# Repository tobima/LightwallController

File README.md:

LightwallController
===================

System
------

Based on the following hardware:
- ARM-Cortex-M4 STM32F407
- STM32F4DIS-BB (Base Board with Ethernet, RS232, MicroSD card slot)

Adaption to the Hardware could be found in the `Hardware folder` ;-)

Software
--------

The manual to setup the development environment can be found at:
http://www.ccc-mannheim.de/wiki/Chibios

After the first download the following script must be executed:
```
InitSubModules.sh
```
Building and flashing:
```
cd Firmware
make
make flash (USB must be reconnected, if flashing failed)
```

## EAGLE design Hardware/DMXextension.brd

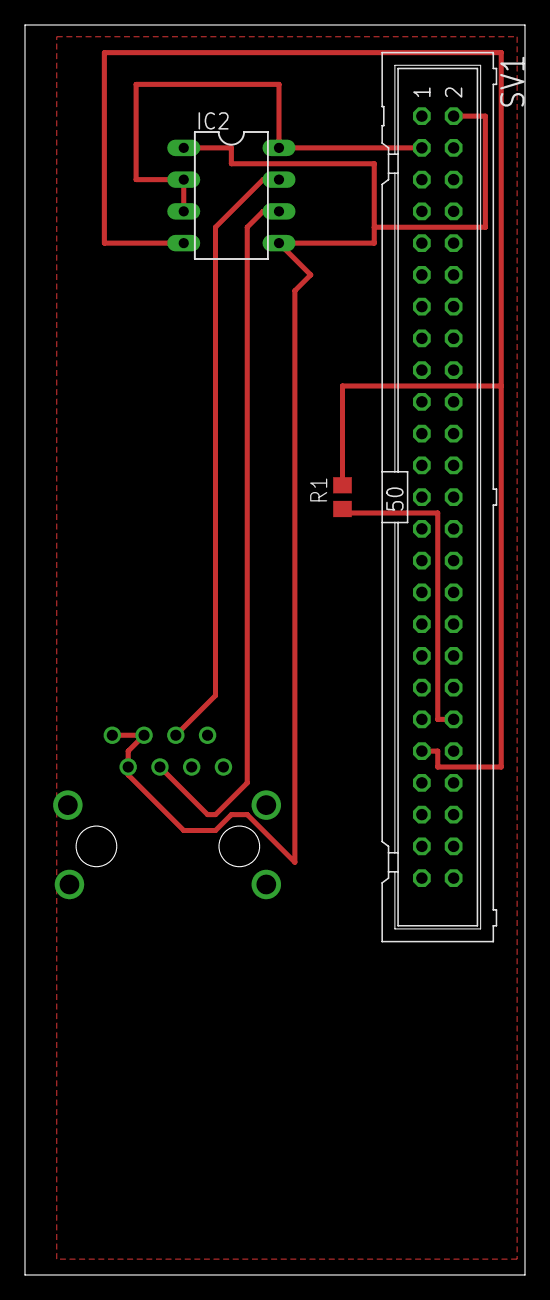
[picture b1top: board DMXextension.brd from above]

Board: 2 copper layers, 40.0 x 100.0 mm, 4 parts (1 on the bottom side), 6 nets.

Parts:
IC2: 75176AP; DIL08
R1: 100; R0805
SV1: ML50
X1: RJ45

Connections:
+5V: IC2.2, IC2.3, IC2.8, SV1.3
GND: IC2.1, IC2.5, SV1.2, X1.6, X1.7, X1.8
GPIOD8: R1.1, SV1.40
GPIOD9: IC2.4, R1.2, SV1.41
unnamed: IC2.7, X1.4
unnamed: IC2.6, X1.5

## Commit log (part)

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2013-05-19 Get USART 6 to work on STMF32DIS-BB evalboard
2013-05-19 add .gitignore
2013-05-26 ethernet stack is working
2013-06-12 Working test system: dmx, sdcard, web server ..
2013-08-24 moved board configuration to own repository
2013-08-24 Updating submodule 'board'
2013-08-28 Update patch for infint loop on mac start
2013-08-28 moved Chibios to lib folder and build folder and Makefile one folder up.
2013-08-28 update board repo
2013-08-28 remove patch. Set ETH1 PHY Power state change to fakse instead.
2013-08-30 Environment cleaning
2013-08-30 Use the Chibios branch of fc_c
2013-08-30 First version of makefile extension in fc_c
2013-08-30 The Makefile uses the fc_c repository
2013-08-30 First try to use fc code in the new environment
2013-09-01 Included the new functionality of fc_c into the project
2013-09-06 Correct aligning for the Microcontroller
2013-09-06 Code for displaying a frame
2013-09-06 Updated fullcircle library
2013-09-22 Upper case and lower case fullcircle files are recogniced
2013-09-27 Some more comments
2013-09-27 Updated Chibios Project
2013-09-27 Small test programm to modify the DMX
2013-09-27 Added some description for the Hardware to build
2013-10-03 Debug interface to display actual DMX buffer
2013-10-03 Restarted DMX project using a random PIN
2013-10-03 More tests with r0ket portation
2013-10-03 Some more comments in DMX
2013-10-03 DMX commandline tool can also decrease the size of the transmitted universe
2013-10-03 Updated the Layout of the DMX extension
2013-10-04 Included some lost changes
2013-10-05 Some measured timings from the Oszi
2013-10-06 Removed unknown code
2013-10-12 Increased the downpull to indicate the start
2013-10-12 Included the routed extension shield
2013-10-18 Added another parameter, to specify the sleeptime between two frames
2013-10-26 Add net shell
2013-10-28 Prepared thread for the dynamic fullcircle protocol
2013-10-28 Endless thread is running until infinity and beyond
2013-10-29 Updated IP address
2013-10-29 Some first steps to use the mailbox
2013-10-29 Also added initialization
2013-10-30 New Fcserver implementation with another callback
2013-11-01 Some tests with the mailbox
2013-11-01 Some more tests
2013-11-01 Reset dmx break time to 125µs
2013-11-01 FC updated
2013-11-01 Mailbox works (again)
2013-11-01 Give the server an pointer to a shell, and he will write on it
2013-11-01 Debugging interface can be activated via commandline + Makefile has necessary define
2013-11-01 add ini parser from https://code.google.com/p/inih/
2013-11-01 Chibios network code
2013-11-01 Only check the mailbox, if there is something inside
2013-11-01 Use new dependency in fc_c
2013-11-01 Better debugging messages
2013-11-01 Deactivated debugging in fc_c library
2013-11-01 wrapped logging for the dynamic fc thread
2013-11-01 Beta Implementation of the server
2013-11-01 Network config could be read from sdcard
2013-11-02 Wrapped comments
2013-11-02 update make rules
2013-11-02 Renamed to other file format
2013-11-02 Moved defines also into the seperate main file
2013-11-05 New library version of fc_c
2013-11-07 Network configuration
2013-11-07 The resolution can be extracted
2013-11-07 Debug output for the mapping logic
2013-11-07 Removed debugging
2013-11-07 Rebuild old code, to give always a new file to the user
2013-11-07 Searching in the root folder of the SDcard is working
2013-11-07 tree command can use a root folder to search in
2013-11-07 The first file is sent back to the user
2013-11-08 Moved sequence file - playing logic into a seperate module
2013-11-08 The files are listed one after the other
2013-11-08 Display only valid paths
2013-11-08 With enough memory sequences can be played automatically
2013-11-08 Initialize the SDcard at the beginning
2013-11-08 Returnvalue for fcstatic_playfile and removed debug comment
2013-11-08 fc_c updated
2013-11-08 Dimming is working
2013-11-08 Removed debug code
2013-11-09 ifconfig has more detailed output; interface can be modified manually
2013-11-09 ifconfig commandline improved
2013-11-09 Refactoring started
2013-11-09 Moved file sending functionality directly into the scheduler
2013-11-09 Blue LED indicating DMX output
2013-11-09 Do not start the fullcircle server thread
2013-11-09 Dynamic server integrated into the Scheduler
2013-11-10 Debuggin in Scheduler decreased
2013-11-11 Fixed status LED
2013-11-12 Button presses are only detected once
2013-11-12 Switch back to final Scheduler logic
2013-11-12 Debug the dynamic protocol again -> Debugging has been activated
2013-11-12 webserver läuftgit add src/web/io.c
2013-11-15 New library
2013-11-15 Removed debug argument
2013-11-15 New configuration reading abstraction
2013-11-15 Cleaned more code from the server logic
2013-11-15 call the mapping functionality from the server functionality
2013-11-16 Finialized interface between fcserver and scheduler
2013-11-26 Comments adapted
2013-11-26 spelling found
2013-11-28 Removed detailed debugging from the configuration
2013-11-29 Beta version of statemachine
2013-11-30 Updated the state diagram
2013-12-06 Interface has its necessary logic
2013-12-06 Blubb
2013-12-06 set the status corretly
2013-12-06 Refactored Mailbox for dynamic server
2013-12-06 New command to disconnect all clients prepared
2013-12-07 New server API is also used correctly on the uC
2013-12-07 Initialize also the return value
2013-12-07 Supervision of the dynamic network code
2013-12-07 Also use milliseconds for the scheduling monitoring
2013-12-07 Only change if we are not deactivated
2013-12-07 Display timeout for incoming frames of the network
2013-12-07 Read configuration
2013-12-07 Corrected configuration parsing (with debugging activated)
2013-12-07 Read the configuration from the SDcard and deactivate the scheduler if necessary
2013-12-12 Gitsubmodule changes
2013-12-27 More debug code
2013-12-27 Started to implement start mechanism for scheduler
2013-12-27 Improved configuration file parsing
2013-12-27 fc library changes
2013-12-28 Changes in the fc library
2013-12-30 Prepared GFX
2013-12-30 Moved copied code from Kaeptn into a new c module
2013-12-30 LEDs neu geordnet
2013-12-30 vprintf into an text buffer (compiling, but more)
2013-12-30 Fixed the orientation of the virtual wall on the LCD Added text output on the screen.
2013-12-30 The client status is visualized on the LCD
2013-12-30 IP address of connecting client is displayed
2013-12-30 Network status codes are displayed in Lightgrey
2013-12-30 Began with timeout visualisazion
2013-12-31 Use another timer for DMX
2014-01-03 Changes the Timer of DMX to another timer
2014-01-03 Moved initialization up into the beginning
2014-01-10 DMX and LCD paralell usage prepared
2014-01-10 Some blank lines moved around
2014-01-12 So nobody must do higher math in his brain
2014-01-12 Reduce compiler warnings
2014-01-13 Shell available via USB
2014-01-13 Found a diff, that was forgotten
2014-02-21 Minimal version generated, where no SDCard or ethernet is supported
2014-03-08 Better Makefile-flag name
2014-03-08 Moved board configuration to a place, where it can be changed (necessary for LCD usage)
2014-03-29 Starting input stuff
2014-04-14 Use a temporary buffer, and only update DMX buffer on valid values
2014-04-14 Added rgb command (all fullcircle lamps)
2014-04-18 Prepared fading with rainbow color algorithm
2014-04-18 Inserted fading algorithm with debug code
2014-04-19 Refactored color fading algorithm, now more portable by using callback function
2014-04-21 fixed makefile, added duration parameter one level deeper
2014-04-21 Added I2C, necessary for touchscreen
2014-04-21 Activate USB Serial interface
2014-04-21 Debug output, when a button was pressed added
2014-04-22 Moved local function to its correct place
2014-04-22 Rebuild visualization with windows
2014-04-22 Second window can be displayed, but is in background :-/
2014-04-22 Overlayed window can coexist
2014-04-22 New module responsible with the logic for the buttons
2014-04-22 Made callbacks for touchscreen accessable for other modules
2014-04-22 Moved calibration it the target
2014-04-22 Storing configuration on FAT (sdcard) in a seperate thread
2014-04-22 activated reading of the configuration
2014-04-22 Added second button, for manual testing logic
2014-04-23 Cleaned up code
2014-04-23 Rearranged SD card initialization
2014-04-23 Comments
2014-04-25 Toggeling manual testing prepared
2014-04-25 Inserted macros for debug output
2014-04-25 Added logic to the manual button (starting the server again is not running)
2014-04-25 First example for accessing the flash added
2014-04-25 Added command into the main function
2014-04-25 Fixed newline
2014-04-25 Still changing
2014-04-25 Starting flashing
2014-04-25 Removed unused files
2014-05-29 Merging complete
2014-05-29 Cleared warning with cast
2014-05-29 Minifixing
2014-05-29 added missing C-sources
2014-05-29 removed redundant code
2014-06-01 Flash test util improved
2014-06-01 removed unused definitions
2014-06-01 better output of the flash test util
2014-06-01 Flash test util can use specific memory blocj
2014-06-01 writing the flash is working
2014-06-01 Touch screen calibration data is stored in the FLASH
2014-06-02 commandline interface for UI added
2014-06-02 debug output when writing into the flash
2014-06-02 insert erasing into access logic to the flash (only used once... timing problem) Also the flash is accessed as one big memory area (no longer block wise)
2014-06-08 Erase flash before storing there a new configuration
2014-06-09 Spelling fixed
2014-06-10 Updated flashing command in the Makefile
2014-06-10 Wait for the fcscheduler to stop
2014-06-11 Project uses FatFswrapping logic
2014-06-11 wrapper successful integrated
2014-06-11 further tweaks in the commandline ugfx util
2014-06-11 Moved the GUI update into the main-loop
2014-06-13 Began with new module for an independet dmx buffer visualization
2014-06-13 more logic inserted in the module to display the DMX on the LCD
2014-06-13 comment
2014-06-13 dummy thread for ugfx tested successfully
2014-06-13 DMX buffer is visualized
2014-06-14 Cleanup of the cleanup
2014-06-18 Added mouse events in order to select a box
2014-06-18 Box can be selected
2014-06-18 Print the coordinate from the select box
2014-06-26 Comments and fixed includes
2014-06-29 First idea of the new interface
2014-06-29 Code is compiling again after the refactoring
2014-06-29 Removed a warning :-)
2014-06-29 fc_c updates
2014-06-30 updated macro disabeling
2014-06-30 display correct framebuffer in debug output
2014-06-30 New GDB configuration integrated
2014-06-30 More checks for the visualization thread
2014-07-05 included new thread to superivise the button
2014-07-05 with more memory, the GUI is displayed
2014-07-05 seperate command added to stop the visualization thread
2014-07-05 Box selection works a little bit better
2014-07-05 Added function to detect boxes hidded by the menu
2014-07-05 Found again a blocking point
2014-07-06 Removed unnecessary function
2014-07-06 Boxes should be selectable
2014-07-06 Initialzation improved
2014-07-06 Changed board submodule
2014-07-06 Updates of the submodules
2014-07-26 Tweaked look and feel
2014-07-26 Display the actual playing file on the HTML page
2014-08-22 Update Chibios to current stable version
2014-11-21 tweaked UART output
2015-03-01 First tests
2015-03-01 Add led strip command interface
2015-03-01 Add the code
2015-03-01 Added LED show command
2015-03-01 Added another module to read the configuration for the LEDs
2015-03-02 Removed Warning
2015-03-02 Merged USBCDC Module into the "old" Lightbox project
2015-03-02 Unique project name inserted
2015-03-02 Made DMX disable and also the dependencies for the filesystem
2015-03-07 Telnet only works with a filesystem
2015-03-07 With the filesystem the controller won't start :-/
2015-03-13 Added the content of the board configuration
2015-03-13 Merged documentation from WookieController (ollo-dev branch)
2015-03-13 Some changes... but no improvements
2015-03-13 Added missing files
2015-03-13 Clean Merged up main.c (from master)
